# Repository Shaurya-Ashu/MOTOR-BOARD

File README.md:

# MOTOR-BOARD
It's a DEV Board specially developed for controlling motors.
We can use this dev board to make anything from a moving car a self balancing robot or even a CNC mill machine.
It's like a all in one mobility powerhouse.

# Why 
 becaue i always wamted one 
 a dev borad which i can directly use to drive a car or make a robotic arm possibilities are endless.
 And also creating a dev board is a fun project.

# BOM
 We have a normal [BOM](BOM/Untitled%20spreadsheet%20-%20BOM.csv)
 & a interactive one https://shaurya-ashu.github.io/MOTOR-BOARD/index.html

# Zine

 It's my first time creating this
 
# Info
It is a dev board based on ESP32-S3-WROOM-1 (My FAV.) mcu, specially designed for multiple types of motors from brushed DC motors, Servo Motors stepper motors etc.

I have used a USB-C port for programming and powering Electronics and the dedicated 3S input for powering the motors.

I have used a INPUT VOLTAGE MULTIPLEXER for selecting between the USB-C power source and battery power source to power the electronics , its is set default to USB power and if USB power is unavailable, then it uses the battery power source.
I get to know about this in a Instagram reel where someone was building custom ESC.

We have to dedicated LDO to convert USB power source and battery power source to 3.3v .
It's a AMS1117-3.3 rated output at 3.3v @1000mah 

It has three peripheral interfaces which you are UART,I2C & SPI .
Which we can use to connect different sensors displays and other devices and also setup a serial communication between two MCU.

Now lets begin with the main part of the schematics the motor drivers and the selector .
So i have used two 3-Way Switches for selecting between diff motors to drive .
we have 2x-TB6612FNG to drive 4x-DC brushless motor

4x-Breakout_A4988 where we can insert A4988 Module to run 4x-Stepper motors.

also to power the servo i have used 2x-ST1S41PHR buck converter so that each servo can get up-to 6v @1A .

Now the the switching part so i have divide it like this in the diagram below :-

Here the vcc enables the drivers for dc-motors & stepper motor and the buck converter for servo's.
The control pins are connected to same pins for for dc-motors , stepper motor & servo .

# Config

 So, all the three thing the dc motor driver , servo & stepper are connected to same GPIO's 
 like this 
 | Net | ESP32-S3 GPIO | Servo Output | A4988 Stepper Driver | TB6612FNG DC Driver |
|:---:|:-------------:|:-------------:|:--------------------:|:-------------------:|
| A1  | GPIO1  | Servo A1 | Stepper 1 ENABLE | M1 PWMA |
| A2  | GPIO2  | Servo A2 | Stepper 1 STEP   | M2 PWMB |
| A3  | GPIO15 | Servo A3 | Stepper 1 DIR    | M1 AIN1 |
| A4  | GPIO4  | Servo A4 | Stepper 2 ENABLE | M1 AIN2 |
| A5  | GPIO5  | Servo A5 | Stepper 2 STEP   | M2 BIN1 |
| A6  | GPIO6  | Servo A6 | Stepper 2 DIR    | M2 BIN2 |
| A7  | GPIO7  | Servo A7 | Stepper 3 ENABLE | M3 PWMA |
| A8  | GPIO22 | Servo A8 | Stepper 3 STEP   | M4 PWMB |
| A9  | GPIO8  | — | Stepper 3 DIR    | M3 AIN1 |
| A10 | GPIO9  | — | Stepper 4 ENABLE | M3 AIN2 |
| A11 | GPIO10 | — | Stepper 4 STEP   | M4 BIN1 |
| A12 | GPIO11 | — | Stepper 4 DIR    | M4 BIN2 |

# PCB

So it's a 4 layer PCB
Confi as:
# Top layer - Signal

# 1 inner layer - GND

# 2 inner layer - Power

# Bottom layer - Signal

the GND layer is divide into two parts then normal electronics and the power/driver electronics and is connected by a single trace .

# Img 

# Build

Just Order the production gerber file from any pcb manufacturer
And other all the components of DigiKey as listed in the bom

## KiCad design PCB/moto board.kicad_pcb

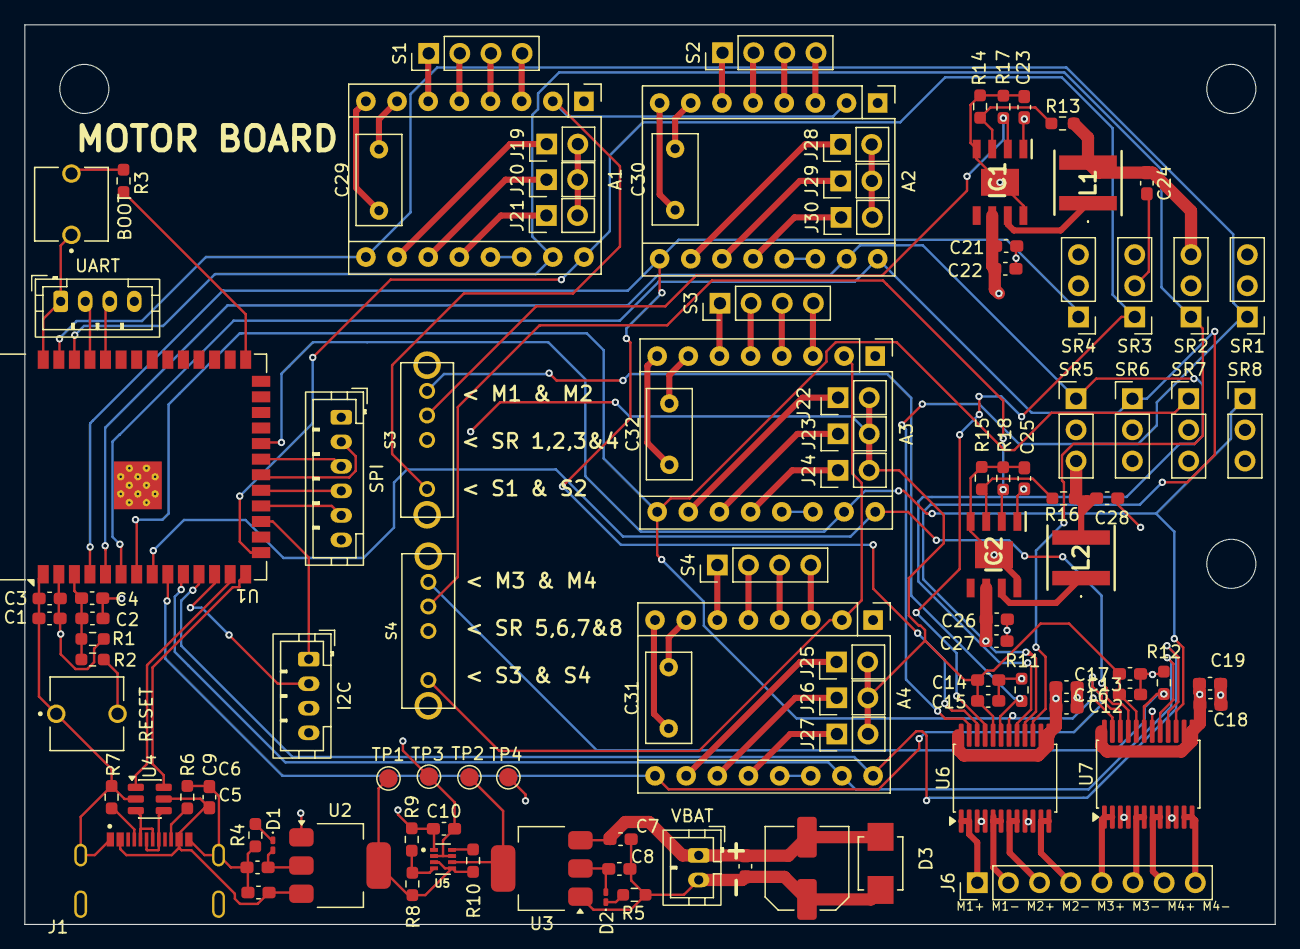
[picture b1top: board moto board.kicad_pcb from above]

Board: 4 copper layers, 102.0 x 73.4 mm, 106 parts (0 on the bottom side), 92 nets.

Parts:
A1, A2, A3, A4: Pololu_Breakout_A4988; Pololu_Breakout-16_15.2x20.3mm
BOOT: BUTT-2; SW_BUTT-2
C1, C5, C6, C7, C8: 22uf; C_0603_1608Metric_Pad1.08x0.95mm_HandSolder
C2, C9, C10, C11, C23, C25: 1uf; C_0603_1608Metric_Pad1.08x0.95mm_HandSolder
C3, C4, C12, C14, C17, C18: 0.1uf; C_0603_1608Metric_Pad1.08x0.95mm_HandSolder
C13, C15, C16, C19, C21, C22, C26, C27: 10uf; C_0603_1608Metric_Pad1.08x0.95mm_HandSolder
C20: 10UF; C_Elec_6.3x5.4
C24, C28: 47uf; C_0603_1608Metric_Pad1.08x0.95mm_HandSolder
C29, C30, C31, C32: 100uf; C_Rect_L7.2mm_W3.5mm_P5.00mm
D1, D2: LED; LED_0201_0603Metric_Pad0.64x0.40mm_HandSolder
D3: SMBJ30CA-13-F; DIOM4336X265N
I2C: Conn_01x04_Pin; JST_PH_B4B-PH-K_1x04_P2.00mm_Vertical
IC1, IC2: ST1S41PHR; SOIC127P600X170-9N
J1: 2340901-1; TE_2340901-1
J6: Conn_01x08_Socket; PinHeader_1x08_P2.54mm_Vertical
J19, J20, J21, J22, J23, J24, J25, J26, J27, J28, J29, J30: Conn_01x02_Pin; PinHeader_1x02_P2.54mm_Vertical
L1, L2: XAL5030-332MEC; XAL5030332MEC
R1, R13, R16: 10k; R_0603_1608Metric_Pad0.98x0.95mm_HandSolder
R2, R3: 0; R_0603_1608Metric_Pad0.98x0.95mm_HandSolder
R4, R5, R10, R11, R12, R17, R18: 1K; R_0603_1608Metric_Pad0.98x0.95mm_HandSolder
R6, R7: 5K1; R_0603_1608Metric_Pad0.98x0.95mm_HandSolder
R8, R9: 47; R_0603_1608Metric_Pad0.98x0.95mm_HandSolder
R14, R15: 68k; R_0603_1608Metric_Pad0.98x0.95mm_HandSolder
RESET: BUTT-2; SW_BUTT-2
S1, S2, S3#2, S4#2: Conn_01x04_Pin; PinHeader_1x04_P2.54mm_Vertical
S3, S4: OS103011MS8QP1; OS102011MS8QP1
SPI: Conn_01x06_Pin; JST_PH_B6B-PH-K_1x06_P2.00mm_Vertical
SR1, SR2, SR3, SR4, SR5, SR6, SR7, SR8: Conn_01x03_Pin; PinHeader_1x03_P2.54mm_Vertical
TP1: VBUS_3.3V; TestPoint_Pad_D1.5mm
TP2: VBAT_3.3V; TestPoint_Pad_D1.5mm
TP3, TP4: TestPoint; TestPoint_Pad_D1.5mm
U1: ESP32-S3-WROOM-1
U2, U3: AMS1117-3.3; SOT-223-3_TabPin2
U4: USBLC6-2SC6; SOT-23-6
U5: TPS2116DRLR; SOTFL50P160X60-8N
U6, U7: TB6612FNG; SSOP-24_5.3x8.2mm_P0.65mm
UART: Conn_01x04_Pin; JST_PH_B4B-PH-K_1x04_P2.00mm_Vertical
VBAT: Conn_01x02_Pin; JST_PH_B2B-PH-K_1x02_P2.00mm_Vertical

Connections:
/6V_1: C24.1, L1.2, R13.1, SR1.3, SR2.3, SR3.3, SR4.3
/6V_2: C28.1, L2.2, R16.1, SR5.3, SR6.3, SR7.3, SR8.3
/A1: A1.9 (~ENABLE), SR1.1, U1.39 (IO1), U6.23 (PWMA)
/A2: A1.15 (STEP), SR2.1, U1.38 (IO2), U6.15 (PWMB)
/A3: A1.16 (DIR), SR3.1, U1.15 (IO3), U6.21 (AIN1)
/A4: A2.9 (~ENABLE), SR4.1, U1.4 (IO4), U6.22 (AIN2)
/A5: A2.15 (STEP), SR5.1, U1.5 (IO5), U6.17 (BIN1)
/A6: A2.16 (DIR), SR6.1, U1.6 (IO6), U6.16 (BIN2)
/A7: A3.9 (~ENABLE), SR7.1, U1.7 (IO7), U7.23 (PWMA)
/A8: A3.15 (STEP), SR8.1, U1.22 (IO14), U7.15 (PWMB)
/A9: A3.16 (DIR), U1.8 (IO15), U7.21 (AIN1)
/A10: A4.9 (~ENABLE), U1.9 (IO16), U7.22 (AIN2)
/A11: A4.15 (STEP), U1.10 (IO17), U7.17 (BIN1)
/A12: A4.16 (DIR), U1.11 (IO18), U7.16 (BIN2)
/BOOT: R3.1, U1.27 (IO0)
/CS: SPI.5, U1.18 (IO10)
/EN: C2.2, C4.2, R1.1, R2.1, U1.3 (EN)
/EN1: IC1.2 (EN), R17.1, S3.3
/EN2: IC2.2 (EN), R18.1, S4.3
/M1: J6.1, U6.1 (AO1), U6.2 (AO1)
/M2: J6.2, U6.5 (AO2), U6.6 (AO2)
/M3: J6.3, U6.7 (BO2), U6.8 (BO2)
/M4: J6.4, U6.11 (BO1), U6.12 (BO1)
/M5: J6.5, U7.1 (AO1), U7.2 (AO1)
/M6: J6.6, U7.5 (AO2), U7.6 (AO2)
/M7: J6.7, U7.7 (BO2), U7.8 (BO2)
/M8: J6.8, U7.11 (BO1), U7.12 (BO1)
/MISO: SPI.3, U1.21 (IO13)
/MOSI: SPI.4, U1.19 (IO11)
/N: U1.13 (USB_D-), U4.1 (I/O1)
/P: U1.14 (USB_D+), U4.6 (I/O1)
/RX: U1.36 (RXD0), UART.3
/SCL: I2C.2, U1.12 (IO8)
/SCLK: SPI.2, U1.20 (IO12)
/SDA: I2C.1, U1.17 (IO9)
/STBY1: R11.1, S3.4, U6.19 (STBY)
/STBY2: R12.1, S4.4, U7.19 (STBY)
/TX: U1.37 (TXD0), UART.2
/USB_DN: J1.A7 (DN1), J1.B7 (DN2), U4.3 (I/O2)
/USB_DP: J1.A6 (DP1), J1.B6 (DP2), U4.4 (I/O2)
/VBAT: A1.8 (VMOT), A2.8 (VMOT), A3.8 (VMOT), A4.8 (VMOT), C7.2, C11.2, C12.2, C13.2, C18.2, C19.2, C20.2, C21.1, C22.1, C23.1, C25.1, C26.1, C27.1, C29.1, C30.1, C31.1, C32.1, D3.1, IC1.1 (VINA), IC1.6 (VINSW), IC2.1 (VINA), IC2.6 (VINSW), U3.3 (VI), U6.13 (VM2), U6.14 (VM3), U6.24 (VM1), U7.13 (VM2), U7.14 (VM3), U7.24 (VM1), VBAT.1
/VBAT_3.3: C8.1, D2.2 (A), TP2.1, U3.2 (VO), U5.6 (VIN2)
/VBUS: C5.2, C9.2, J1.A4/B9 (VBUS_A), J1.B4/AP (VBUS_B), U2.3 (VI), U4.5 (VBUS)
/VBUS_3.3: C6.1, D1.2 (A), R8.2, R10.2, TP1.1, U2.2 (VO), U5.3 (VIN1), U5.5 (MODE)
/vdd_s1: A1.2 (VDD), A2.2 (VDD), S3.1
/vdd_s2: A3.2 (VDD), A4.2 (VDD), S4.1
GND: A1.1 (GND), A1.7 (GND), A2.1 (GND), A2.7 (GND), A3.1 (GND), A3.7 (GND), A4.1 (GND), A4.7 (GND), BOOT.1, C1.1, C2.1, C3.1, C4.1, C5.1, C6.2, C7.1, C8.2, C9.1, C10.1, C11.1, C12.1, C13.1, C14.1, C15.1, C16.1, C17.1, C18.1, C19.1, C20.1, C21.2, C22.2, C23.2, C24.2, C25.2, C26.2, C27.2, C28.2, C29.2, C30.2, C31.2, C32.2, D3.2, I2C.3, IC1.4 (GND), IC1.8 (PGND), IC1.9 (EPAD), IC2.4 (GND), IC2.8 (PGND), IC2.9 (EPAD), J1.A1/B12 (GND_A), J1.B1/A12 (GND_B), J1.SH1 (SHIELD), J1.SH2 (SHIELD), J1.SH3 (SHIELD), J1.SH4 (SHIELD), R4.2, R5.2, R6.2, R7.1, R9.2, R11.2, R12.2, R14.2, R15.2, R17.2, R18.2, RESET.1, SPI.6, SR1.2, SR2.2, SR3.2, SR4.2, SR5.2, SR6.2, SR7.2, SR8.2, TP4.1, U1.1 (GND), U1.40 (GND), U1.41 (GND), U2.1 (GND), U3.1 (GND), U4.2 (GND), U5.1 (GND), U6.3 (PGND1), U6.4 (PGND1), U6.9 (PGND2), U6.10 (PGND2), U6.18 (GND), U7.3 (PGND1), U7.4 (PGND1), U7.9 (PGND2), U7.10 (PGND2), U7.18 (GND), UART.1, VBAT.2
unnamed: A1.4 (1A), S1.3
unnamed: A1.3 (1B), S1.4
unnamed: A1.5 (2A), S1.2
unnamed: A1.6 (2B), S1.1
unnamed: A1.10 (MS1), J19.1
unnamed: A1.11 (MS2), J20.1
unnamed: A1.12 (MS3), J21.1
unnamed: A1.13 (~RESET), A1.14 (~SLEEP)
unnamed: A2.4 (1A), S2.3
unnamed: A2.3 (1B), S2.4
unnamed: A2.5 (2A), S2.2
unnamed: A2.6 (2B), S2.1
unnamed: A2.10 (MS1), J28.1
unnamed: A2.11 (MS2), J29.1
unnamed: A2.12 (MS3), J30.1
unnamed: A2.13 (~RESET), A2.14 (~SLEEP)
unnamed: A3.4 (1A), S3#2.3
unnamed: A3.3 (1B), S3#2.4
unnamed: A3.5 (2A), S3#2.2
unnamed: A3.6 (2B), S3#2.1
unnamed: A3.10 (MS1), J22.1
unnamed: A3.11 (MS2), J23.1
unnamed: A3.12 (MS3), J24.1
unnamed: A3.13 (~RESET), A3.14 (~SLEEP)
unnamed: A4.4 (1A), S4#2.3
unnamed: A4.3 (1B), S4#2.4
unnamed: A4.5 (2A), S4#2.2
unnamed: A4.6 (2B), S4#2.1
unnamed: A4.10 (MS1), J25.1
unnamed: A4.11 (MS2), J26.1
unnamed: A4.12 (MS3), J27.1
unnamed: A4.13 (~RESET), A4.14 (~SLEEP)
unnamed: D1.1 (K), R4.1
unnamed: D2.1 (K), R5.1
unnamed: IC1.3 (FB), R13.2, R14.1
unnamed: IC1.7 (SW), L1.1
unnamed: IC2.3 (FB), R15.1, R16.2
unnamed: IC2.7 (SW), L2.1
unnamed: J1.A5 (CC1), R7.2
unnamed: J1.B5 (CC2), R6.1
unnamed: R2.2, RESET.2
unnamed: BOOT.2, R3.2
unnamed: R8.1, R9.1, U5.4 (PR1)
unnamed: R10.1, U5.8 (ST)
VCC: C1.2, C3.2, C10.2, C14.2, C15.2, C16.2, C17.2, I2C.4, J19.2, J20.2, J21.2, J22.2, J23.2, J24.2, J25.2, J26.2, J27.2, J28.2, J29.2, J30.2, R1.2, S3.2, S4.2, SPI.1, TP3.1, U1.2 (3V3), U5.2 (VOUT), U5.7 (VOUT), U6.20 (VCC), U7.20 (VCC), UART.4

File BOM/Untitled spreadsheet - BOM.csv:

BILL OF MATERIALS ,,,,,,,
Item No.,Reference(s),Description,Footprint / Package,Qty,Unit Price (USD),Total Value (USD),Purchase Link
1,"A1, A2, A3, A4",Pololu A4988 Stepper Motor Driver Breakout (Black Ed.),Module 15.2×20.3 mm (16-pin),4,$5.95,$23.80,https://www.pololu.com/product/2128
2,"C1, C5, C6, C7, C8","Capacitor, 22 µF, SMD 0603",C_0603_1608Metric HandSolder,5,$0.12,$0.60,https://www.digikey.com/en/products/filter/ceramic-capacitor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
3,"C2, C9, C10, C11, C23, C25","Capacitor, 1 µF, SMD 0603",C_0603_1608Metric HandSolder,6,$0.10,$0.60,https://www.digikey.com/en/products/filter/ceramic-capacitors/60
4,"C3, C4, C12, C14, C17, C18","Capacitor, 100 nF (0.1 µF), SMD 0603",C_0603_1608Metric HandSolder,6,$0.08,$0.48,https://www.digikey.com/en/products/filter/ceramic-capacitors/60
5,"C13, C15, C16, C19, C21, C22, C26, C27","Capacitor, 10 µF, SMD 0603",C_0603_1608Metric HandSolder,8,$0.15,$1.20,https://www.digikey.com/en/products/filter/ceramic-capacitors/60
6,C20,"Capacitor, 10 µF, Electrolytic THT",C_Elec 6.3×5.4 mm,1,$0.20,$0.20,https://www.digikey.com/en/products/filter/aluminum-electrol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
7,"C24, C28","Capacitor, 47 µF, SMD 0603",C_0603_1608Metric HandSolder,2,$0.22,$0.44,https://www.digikey.com/en/products/filter/ceramic-capacitors/60
8,"C29, C30, C31, C32","Capacitor, 100 µF, Electrolytic THT",C_Rect L7.2×W3.5 mm P5.00 mm,4,$0.25,$1.00,https://www.digikey.com/en/products/filter/aluminum-electrol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
9,"D1, D2","LED, General Purpose, SMD 0201 (0603 pads)",LED_0201_0603Metric HandSolder,2,$0.10,$0.20,https://www.digikey.com/en/products/filter/leds-through-hole/93
10,D3,SMBJ30CA-13-F — 30 V Bidirectional TVS Diode,SMB (DO-214AA) / DIOM4336,1,$0.55,$0.55,https://www.digikey.com/en/products/detail/diodes-incorporat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
11,"IC1, IC2",ST1S41PHR — 3 A Step-Down Switching Regulator,SOIC-9 (SOIC127P600X170-9N),2,$1.85,$3.70,https://www.mouser.com/ProductDetail/STMicroelectronics/ST1S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
12,J1,2340901-1 — TE Connectivity Connector,TE_2340901-1,1,$1.20,$1.20,https://www.digikey.com/en/products/detail/te-connectivity-a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
13,J2,JST PH 2-Pin Vertical Connector (2.00 mm pitch),JST_PH B2B-PH-K 1×02 P2.00 mm,1,$0.35,$0.35,https://www.digikey.com/en/products/detail/jst-sales-america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
14,"J3, J5",JST PH 4-Pin Vertical Connector (2.00 mm pitch),JST_PH B4B-PH-K 1×04 P2.00 mm,2,$0.45,$0.90,https://www.digikey.com/en/products/detail/jst-sales-america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
15,J4,JST PH 6-Pin Vertical Connector (2.00 mm pitch),JST_PH B6B-PH-K 1×06 P2.00 mm,1,$0.55,$0.55,https://www.digikey.com/en/products/detail/jst-sales-america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
16,J6,1×8 Female Pin Header 2.54 mm pitch,PinHeader_1×08 P2.54 mm Vertical,1,$0.30,$0.30,https://www.digikey.com/en/products/filter/rectangular-conne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
17,J7–J14 (8 pcs),1×3 Male Pin Header 2.54 mm pitch,PinHeader_1×03 P2.54 mm Vertical,8,$0.10,$0.80,https://www.digikey.com/en/products/filter/rectangular-conne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
18,"J15, J16, J17, J18",1×4 Male Pin Header 2.54 mm pitch,PinHeader_1×04 P2.54 mm Vertical,4,$0.12,$0.48,https://www.digikey.com/en/products/filter/rectangular-conne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
19,J19–J30 (12 pcs),1×2 Male Pin Header 2.54 mm pitch,PinHeader_1×02 P2.54 mm Vertical,12,$0.08,$0.96,https://www.digikey.com/en/products/filter/rectangular-conne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
20,"L1, L2",XAL5030-332MEC — 3.3 µH 4.7 A Shielded Power Inductor,XAL5030 (5×5×3 mm),2,$1.98,$3.96,https://www.mouser.com/ProductDetail/Coilcraft/XAL5030-332ME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
21,"R1, R13, R16","Resistor, 10 kΩ, SMD 0603",R_0603_1608Metric HandSolder,3,$0.05,$0.15,https://www.digikey.com/en/products/filter/chip-resistor-sur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
22,"R2, R3","Resistor, 0 Ω (Jumper), SMD 0603",R_0603_1608Metric HandSolder,2,$0.05,$0.10,https://www.digikey.com/en/products/filter/chip-resistor-sur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
23,"R4, R5, R10, R11, R12, R17, R18","Resistor, 1 kΩ, SMD 0603",R_0603_1608Metric HandSolder,7,$0.05,$0.35,https://www.digikey.com/en/products/filter/chip-resistor-sur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
24,"R6, R7","Resistor, 5.1 kΩ, SMD 0603",R_0603_1608Metric HandSolder,2,$0.05,$0.10,https://www.digikey.com/en/products/filter/chip-resistor-sur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
25,"R8, R9","Resistor, 47 Ω, SMD 0603",R_0603_1608Metric HandSolder,2,$0.05,$0.10,https://www.digikey.com/en/products/filter/chip-resistor-sur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
26,"R14, R15","Resistor, 68 kΩ, SMD 0603",R_0603_1608Metric HandSolder,2,$0.05,$0.10,https://www.digikey.com/en/products/filter/chip-resistor-sur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
27,"S1, S2",Tactile Push Button (BUTT-2),SW_BUTT-2,2,$0.25,$0.50,https://www.digikey.com/en/products/filter/tactile-switches/197
28,"S3, S4",OS103011MS8QP1 — SPDT Slide Switch,OS103011MS8QP1,2,$0.45,$0.90,https://www.digikey.com/en/products/detail/c-k/OS103011MS8QP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
29,TP1,Test Point — VBUS 3.3 V,TestPoint_Pad D1.5 mm,1,$0.05,$0.05,https://www.digikey.com/en/products/filter/test-points/639
30,TP2,Test Point — VBAT 3.3 V,TestPoint_Pad D1.5 mm,1,$0.05,$0.05,https://www.digikey.com/en/products/filter/test-points/639
31,"TP3, TP4",Test Point — General Purpose,TestPoint_Pad D1.5 mm,2,$0.05,$0.10,https://www.digikey.com/en/products/filter/test-points/639
32,U1,ESP32-S3-WROOM-1 — WiFi/BT5 Module (PCB ant.),RF_Module:ESP32-S3-WROOM-1,1,$3.50,$3.50,https://www.digikey.com/en/products/detail/espressif-systems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
33,"U2, U3",AMS1117-3.3 — 1 A LDO Voltage Regulator 3.3 V,SOT-223-3 TabPin2,2,$0.30,$0.60,https://www.digikey.com/en/products/detail/umw/AMS1117-3.3/17084460
34,U4,"USBLC6-2SC6 — USB ESD Protection, SOT-23-6",SOT-23-6,1,$0.54,$0.54,https://www.digikey.com/en/products/detail/stmicroelectronic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
35,U5,TPS2116DRLR — Power Mux / Priority Switch,SOT-FL50P160×60-8N (VSON-8),1,$0.80,$0.80,https://www.digikey.com/en/products/detail/texas-instruments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
36,"U6, U7",TB6612FNG — Dual H-Bridge DC Motor Driver,SSOP-24 5.3×8.2 mm P0.65 mm,2,$2.72,$5.44,https://www.digikey.com/en/products/detail/toshiba-semicondu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
37,PCB,PCB,--,5,$1.40,$7.00,NA
GRAND TOTAL (USD),,,,,,$62.65,

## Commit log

2026-06-10 Create A
2026-06-10 Create f
2026-06-10 Create h
2026-06-10 Rename ibom.html to index.html
2026-06-10 Rename BOM/index.html to index.html
2026-06-11 Create J
2026-06-11 Create Production file
2026-06-11 Rename PCB/moto board_101.95x73.35mm_for_Default.zip to Production_Gerber.zip
2026-06-12 Create g
2026-06-12 Rename moto board_101.95x73.35mm_for_Default.zip to moto board_Gerber.zip
